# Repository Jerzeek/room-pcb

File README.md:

# Room Sensor

An open-source, mains-powered room sensor PCB based on the ESP32-C6. Measures CO2, temperature, humidity, illuminance, and presence, with a WS2812B LED status indicator. Supports both **ESPHome** (Wi-Fi / Home Assistant) and **Zigbee** firmware out of the box.

---

> **WARNING — MAINS AC VOLTAGE**
>
> This board connects directly to mains AC (100–240 V). Incorrect wiring or handling can cause **electric shock, fire, or death**. This project is intended for **experienced makers** who are comfortable working with mains-voltage electronics. Always work with the power disconnected. Comply with all local electrical codes. The authors accept no liability for any damage or injury.

---

## Features

- Direct mains AC input via onboard HLK-5M05 AC-DC converter (no external power brick needed)
- CO2, temperature, and humidity via CozIR sensor (NDIR CO2, UART)
- Ambient light via BH1750 (I2C, lux)
- Secondary temperature + humidity via AHT20 (I2C)
- Presence/occupancy detection via LD2410 mmWave radar (UART)
- Visual CO2 status indicator: 2× WS2812B addressable LEDs
- Polyfuse (F1) overcurrent protection
- Reset/factory-reset button (BOOT pin)
- ESP32-C6 SuperMini module — supports both Wi-Fi 6 and native Zigbee
- Two equal-priority firmware options: ESPHome and Zigbee (Arduino)

## Sensors

| Sensor | Part | Interface | Measures |
|---|---|---|---|
| CO2 (NDIR) | CozIR | UART (9600 baud) | CO2 (ppm), temperature, humidity |
| Ambient light | BH1750FVI-TR | I2C (0x23) | Illuminance (lux) |
| Temperature + humidity | AHT20 | I2C | Temperature (°C), humidity (%RH) |
| Presence / occupancy | LD2410 | UART (256000 baud) | Presence, moving/stationary targets |
| Status LEDs | WS2812B-2020 × 2 | GPIO (RMT) | CO2 level indicator |

## Hardware

### Main components

| Ref | Part | Description |
|---|---|---|
| U5 | ESP32-C6 SuperMini | Main MCU — Wi-Fi 6 + Zigbee |
| PS1 | HLK-5M05 | AC-DC converter, 100–240 V AC → 5 V DC |
| U1 | CozIR | NDIR CO2 / temp / humidity sensor |
| U2 | BH1750FVI-TR | Ambient light sensor |
| U3 | AHT20 | Temperature + humidity sensor |
| J4 | 5-pin header (1.27 mm) | LD2410 radar connection |
| D1, D2 | WS2812B-2020 | Addressable RGB LEDs |
| F1 | Polyfuse | Overcurrent protection |

### Versions

| Version | Notes |
|---|---|
| v4.1 | Current release — improved silkscreen |
| v4 | Production-ready layout |
| v3.1 | Earlier revision (3D model reference) |
| v3 | Initial working prototype |

## Building / Ordering

All files needed to order and assemble the PCB are in `pcb/production/`:

| File | Purpose |
|---|---|
| `room-pcb.zip` | Gerber + drill files — upload directly to your PCB fab (JLCPCB, PCBWay, etc.) |
| `bom.csv` | Bill of materials for component sourcing |
| `positions.csv` | Pick-and-place / component placement file |
| `designators.csv` | Designator reference |
| `netlist.ipc` | IPC-D-356 netlist for electrical testing |

KiCad source files are in `pcb/`.

## Firmware

### ESPHome (Wi-Fi / Home Assistant)

Configuration is in `code/esphome/room_sensor.yaml`. A custom ESPHome component for the CozIR sensor is included under `code/esphome/components/cozir/`.

1. Copy `room_sensor.yaml` and the `components/` directory to your ESPHome config folder.
2. Create a `secrets.yaml` with your `wifi_ssid` and `wifi_password`.
3. Flash via `esphome run room_sensor.yaml`.

The LED indicates CO2 level:

| Color | CO2 |
|---|---|
| Green | < 800 ppm (good) |
| Yellow | 800–1200 ppm (moderate) |
| Red | > 1200 ppm (poor) |

Calibration buttons are exposed to Home Assistant:
- **Calibrate Fresh Air (400 ppm)** — use outdoors in clean air
- **Calibrate Nitrogen (0 ppm)** — use with pure N2

### Zigbee (Arduino / esp32-arduino)

Sketch is in `code/combined_working_zigbee/combined_working_zigbee.ino`. Requires the Arduino ESP32 core (≥ 3.x) with Zigbee support.

**Before flashing:**
- In Arduino IDE → Tools → Zigbee Mode → select **Zigbee ED (End Device)**
- Select a partition scheme that includes Zigbee (e.g., *Zigbee 4MB with spiffs*)

The sketch exposes four Zigbee endpoints:

| Endpoint | Cluster | Data |
|---|---|---|
| 10 | CO2 (CarbonDioxide) | CO2 ppm |
| 11 | Temp + Humidity | Temperature °C, humidity %RH |
| 13 | Illuminance | Lux |
| 14 | Occupancy | Presence (boolean) |

Hold the BOOT button for 3 seconds to perform a Zigbee factory reset.

## Repository layout

```
room-pcb/
├── pcb/                  KiCad project files
│   └── production/       Gerbers, BOM, placement — ready to order
├── code/
│   ├── esphome/          ESPHome YAML + custom CozIR component
│   └── combined_working_zigbee/  Arduino Zigbee sketch
├── 3Dmodels/             STEP model of the enclosure / board
├── CHANGELOG.md
├── CONTRIBUTING.md
└── LICENSE
```

## License

Hardware (PCB and schematics) is licensed under the **CERN Open Hardware Licence Version 2 — Strongly Reciprocal (CERN OHL-S v2)**. See [LICENSE](LICENSE) for the full text.

Firmware is licensed under the same CERN OHL-S v2 unless a file header states otherwise.

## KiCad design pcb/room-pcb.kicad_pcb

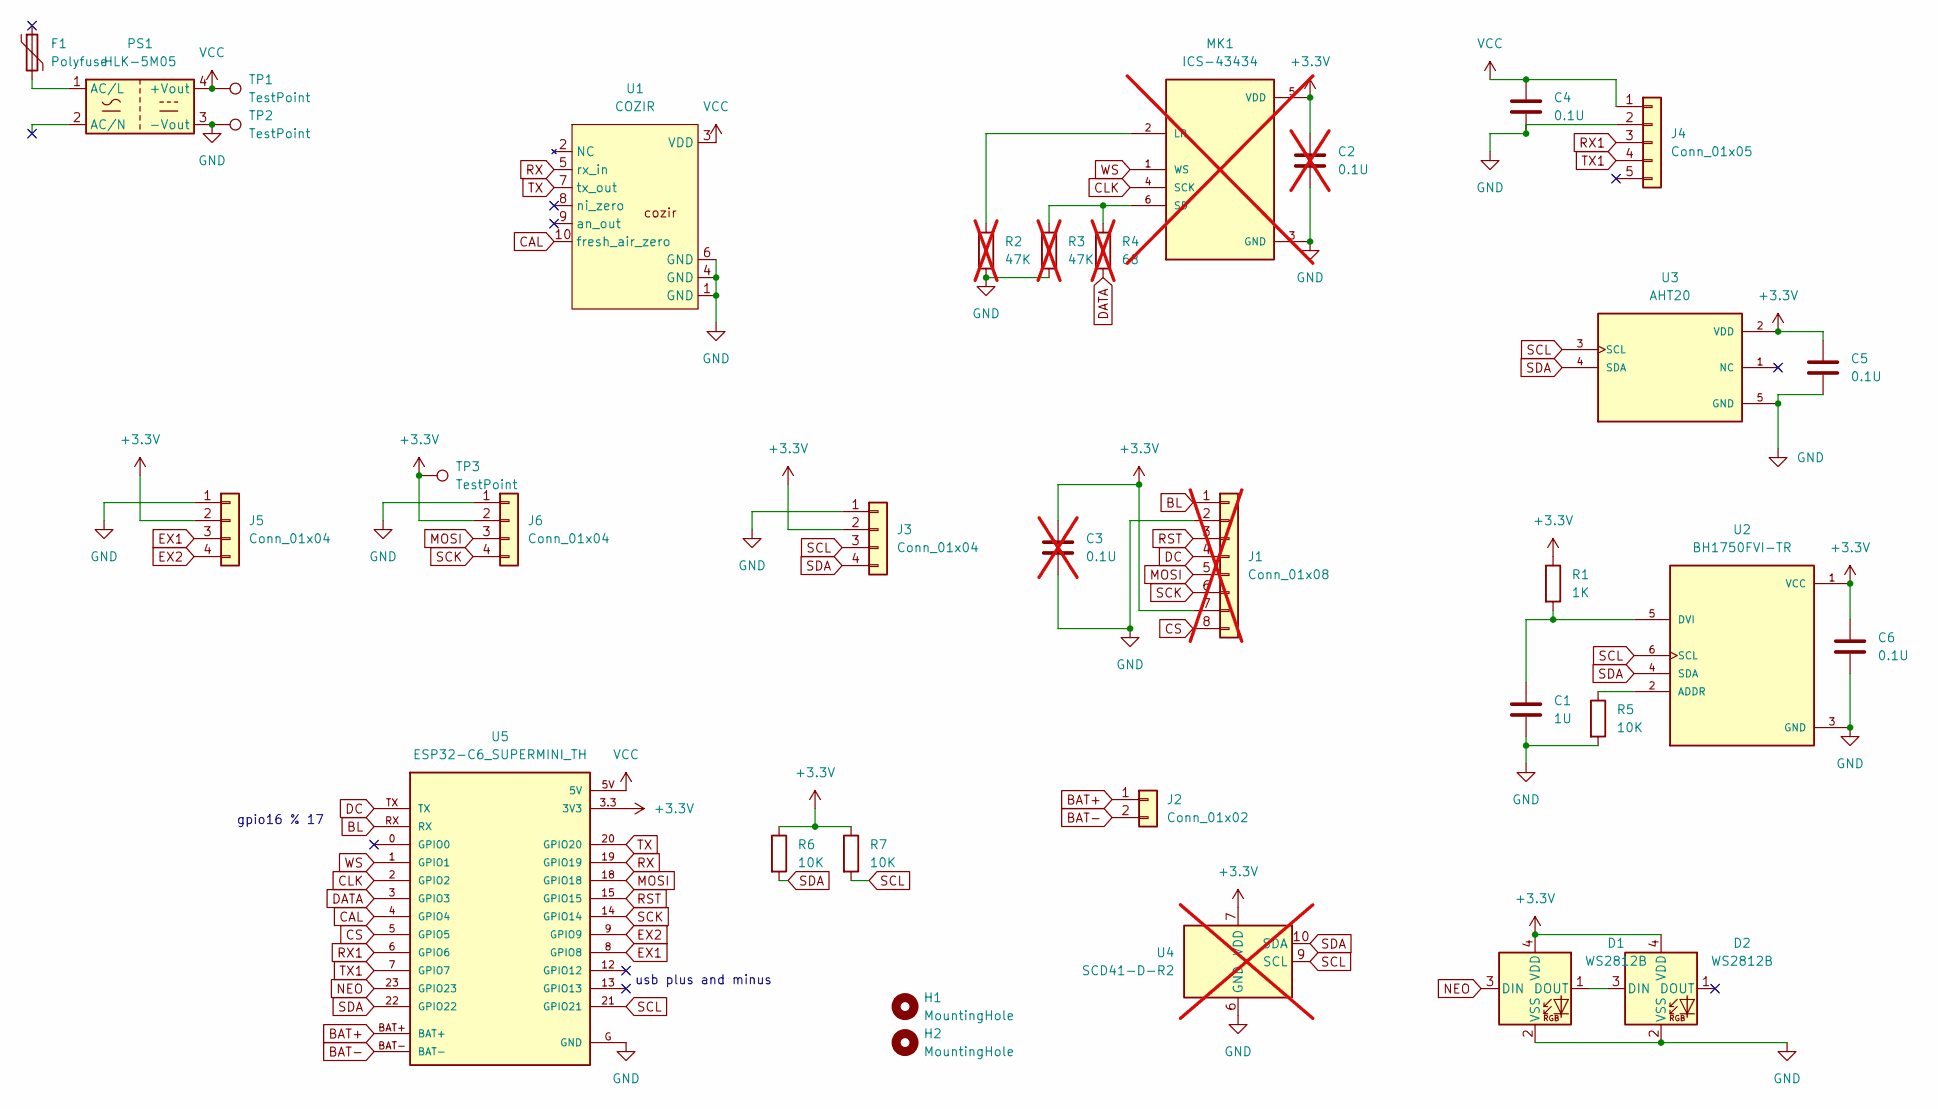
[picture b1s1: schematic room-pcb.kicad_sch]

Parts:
C1: 1U; C_0805_2012Metric
C2, C3: 0.1U; C_0805_2012Metric; not fitted
C4, C5, C6: 0.1U; C_0805_2012Metric
D1, D2: WS2812B; LED_WS2812B-2020_PLCC4_2.0x2.0mm
F1: Polyfuse; Fuse_Bourns_MF-RG300
H1, H2: MountingHole; MountingHole_3.2mm_M3
J1: Conn_01x08; Hirose_FH12-8S-0.5SH_1x08-1MP_P0.50mm_Horizontal; not fitted
J2: Conn_01x02; JST_PH_S2B-PH-SM4-TB_1x02-1MP_P2.00mm_Horizontal
J3: Conn_01x04; JST_SH_SM04B-SRSS-TB_1x04-1MP_P1.00mm_Horizontal
J4: Conn_01x05; PinHeader_1x05_P1.27mm_Vertical
J5, J6: Conn_01x04; PinHeader_1x04_P2.54mm_Vertical
MK1: ICS-43434; MIC_ICS-43434; not fitted
PS1: HLK-5M05; Converter_ACDC_Hi-Link_HLK-5Mxx
R1: 1K; R_0805_2012Metric
R2, R3: 47K; R_0805_2012Metric; not fitted
R4: 68; R_0805_2012Metric; not fitted
R5, R6, R7: 10K; R_0805_2012Metric
TP1, TP2, TP3: TestPoint; TestPoint_THTPad_D1.5mm_Drill0.7mm
U1: COZIR; cozir
U2: BH1750FVI-TR; XDCR_BH1750FVI-TR; PARTREV D
U3: AHT20; PSON100P300X300X110-6N; PARTREV V1.0
U4: SCD41-D-R2; Sensirion_SCD4x-1EP_10.1x10.1mm_P1.25mm_EP4.8x4.8mm; not fitted
U5: ESP32-C6_SUPERMINI_TH; MODULE_ESP32-C6_SUPERMINI_TH

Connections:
+3.3V: C2.1, C3.1, C5.1, C6.1, D1.4 (VDD), D2.4 (VDD), J1.7, J3.2, J5.2, J6.2, MK1.5 (VDD), R1.1, R6.1, R7.1, TP3.1, U2.1 (VCC), U3.2 (VDD), U4.7 (VDD), U4.19 (VDD), U5.3.3 (3V3)
BAT+: J2.1, U5.BAT+
BAT-: J2.2, U5.BAT-
BL: J1.1, U5.RX
CAL: U1.10 (fresh_air_zero), U5.4 (GPIO4)
CLK: MK1.4 (SCK), U5.2 (GPIO2)
CS: J1.8, U5.5 (GPIO5)
DATA: R4.2, U5.3 (GPIO3)
DC: J1.4, U5.TX
EX1: J5.3, U5.8 (GPIO8)
EX2: J5.4, U5.9 (GPIO9)
GND: C1.2, C2.2, C3.2, C4.2, C5.2, C6.2, D1.2 (VSS), D2.2 (VSS), J1.2, J3.1, J4.2, J5.1, J6.1, MK1.3 (GND), PS1.3 (-Vout), R2.2, R3.2, R5.2, TP2.1, U1.1 (GND), U1.4 (GND), U1.6 (GND), U2.3 (GND), U3.5 (GND), U4.6 (GND), U4.20 (GND), U4.21 (GND), U5.G (GND)
MOSI: J1.5, J6.3, U5.18 (GPIO18)
NEO: D1.3 (DIN), U5.23 (GPIO23)
unnamed: D1.1 (DOUT), D2.3 (DIN)
unnamed: MK1.2 (LR), R2.1
unnamed: MK1.6 (SD), R3.1, R4.1
unnamed: F1.2, PS1.1 (AC/L)
unnamed: R5.1, U2.2 (ADDR)
unnamed: C1.1, R1.2, U2.5 (DVI)
RST: J1.3, U5.15 (GPIO15)
RX: U1.5 (rx_in), U5.19 (GPIO19)
RX1: J4.3, U5.6 (GPIO6)
SCK: J1.6, J6.4, U5.14 (GPIO14)
SCL: J3.3, R7.2, U2.6 (SCL), U3.3 (SCL), U4.9 (SCL), U5.21 (GPIO21)
SDA: J3.4, R6.2, U2.4 (SDA), U3.4 (SDA), U4.10 (SDA), U5.22 (GPIO22)
TX: U1.7 (tx_out), U5.20 (GPIO20)
TX1: J4.4, U5.7 (GPIO7)
VCC: C4.1, J4.1, PS1.4 (+Vout), TP1.1, U1.3 (VDD), U5.5V
WS: MK1.1 (WS), U5.1 (GPIO1)

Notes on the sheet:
gpio16 % 17
usb plus and minus

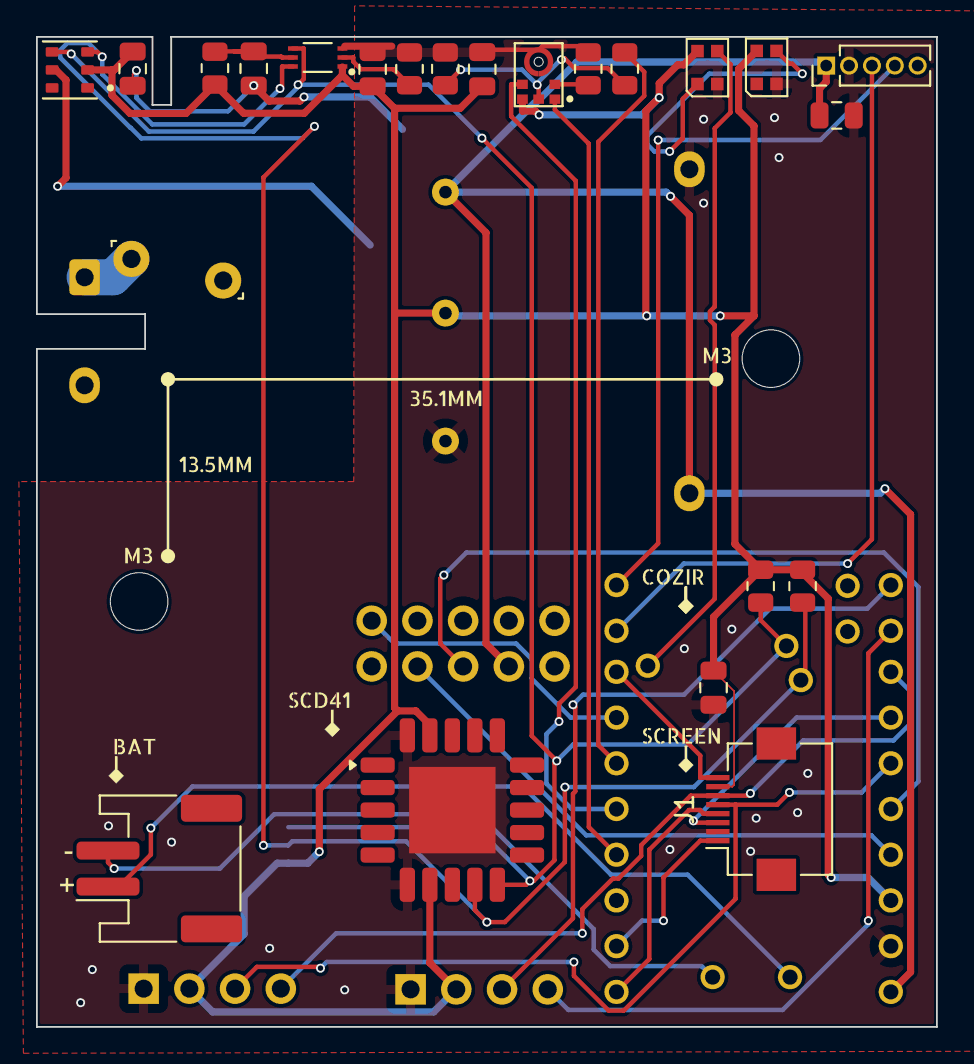
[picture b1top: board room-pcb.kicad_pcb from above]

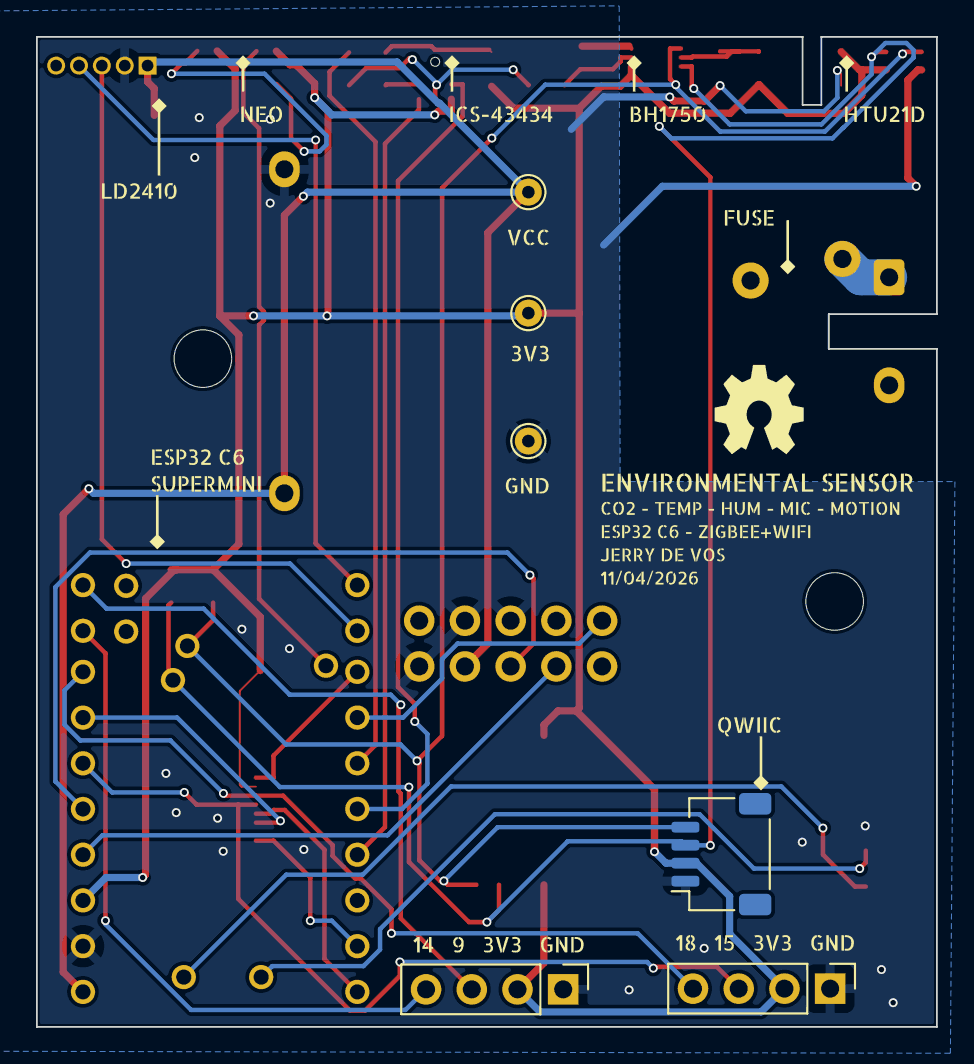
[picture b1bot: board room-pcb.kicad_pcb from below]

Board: 2 copper layers, 50.0 x 55.0 mm, 34 parts (7 on the bottom side), 30 nets.

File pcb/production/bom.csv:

Designator,Footprint,Quantity,Value,LCSC Part #
C1,0805,1,1U,
"C4, C5, C6",0805,3,0.1U,
"D1, D2",LED_WS2812B-2020_PLCC4_2.0x2.0mm,2,WS2812B,
F1,Fuse_Bourns_MF-RG300,1,Polyfuse,
J2,JST_PH_S2B-PH-SM4-TB_1x02-1MP_P2.00mm_Horizontal,1,Conn_01x02,
J3,JST_SH_SM04B-SRSS-TB_1x04-1MP_P1.00mm_Horizontal,1,Conn_01x04,
J4,PinHeader_1x05_P1.27mm_Vertical,1,Conn_01x05,
"J5, J6",PinHeader_1x04_P2.54mm_Vertical,2,Conn_01x04,
PS1,Converter_ACDC_Hi-Link_HLK-5Mxx,1,HLK-5M05,
R1,0805,1,1K,
"R5, R6, R7",0805,3,10K,
"TP1, TP2, TP3",TestPoint_THTPad_D1.5mm_Drill0.7mm,3,TestPoint,
U1,cozir,1,COZIR,
U2,XDCR_BH1750FVI-TR,1,BH1750FVI-TR,
U3,PSON100P300X300X110-6N,1,AHT20,
U5,MODULE_ESP32-C6_SUPERMINI_TH,1,ESP32-C6_SUPERMINI_TH,

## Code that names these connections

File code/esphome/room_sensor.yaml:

esphome:
  name: room-sensor3
  friendly_name: room_sensor3

esp32:
  board: esp32-c6-devkitc-1
  framework:
    type: esp-idf

# Enable logging
logger:

# Enable Home Assistant API
api:
  encryption:
    key: "x7dmEtUnraoTiORhJYHz7vtC5tRRsgen1eWqUg1EyWk="

ota:
  - platform: esphome
    password: "e07e7f460b2b8dd917edea576c4c2a43"

wifi:
  ssid: !secret wifi_ssid
  password: !secret wifi_password

  # Enable fallback hotspot (captive portal) in case wifi connection fails
  ap:
    ssid: "Room-Sensor Fallback Hotspot"
    password: "viXdy4Uy5Z67"

captive_portal:

external_components:
  - source:
      type: local
      path: components

uart:

  - id: uart_bus
    tx_pin: GPIO19
    rx_pin: GPIO20
    baud_rate: 9600

  - id: uart_bus_ld2410
    tx_pin: GPIO5
    rx_pin: GPIO7
    baud_rate: 256000 
    parity: NONE
    stop_bits: 1

i2c:
  sda: GPIO22
  scl: GPIO21

# Example configuration entry
ld2410:
  - uart_id: uart_bus_ld2410

light:
  - platform: esp32_rmt_led_strip
    rgb_order: GRB
    id: co2_led
    pin: GPIO23
    num_leds: 2
    chipset: ws2812
    name: "My Light"

binary_sensor:
  - platform: ld2410
    has_target:
      name: Presence
    # has_moving_target:
    #   name: Moving Target
    # has_still_target:
    #   name: Still Target
    # out_pin_presence_status:
    #   name: Out pin presence status

sensor:
  # - platform: ld2410
  #   light:
  #     name: Light
  #   moving_distance:
  #     name: Moving Distance
  #   still_distance:
  #     name: Still Distance
  #   moving_energy:
  #     name: Move Energy
  #   still_energy:
  #     name: Still Energy
  #   detection_distance:
  #     name: Detection Distance
  #   g0:
  #     move_energy:
  #       name: G0 move energy
  #     still_energy:
  #       name: G0 still energy
  #   g1:
  #     move_energy:
  #       name: G1 move energy
  #     still_energy:
  #       name: G1 still energy
  #   g2:
  #     move_energy:
  #       name: G2 move energy
  #     still_energy:
  #       name: G2 still energy
  #   g3:
  #     move_energy:
  #       name: G3 move energy
  #     still_energy:
  #       name: G3 still energy
  #   g4:
  #     move_energy:
  #       name: G4 move energy
  #     still_energy:
  #       name: G4 still energy
  #   g5:
  #     move_energy:
  #       name: G5 move energy
  #     still_energy:
  #       name: G5 still energy
  #   g6:
  #     move_energy:
  #       name: G6 move energy
  #     still_energy:
  #       name: G6 still energy
  #   g7:
  #     move_energy:
  #       name: G7 move energy
  #     still_energy:
  #       name: G7 still energy
  #   g8:
  #     move_energy:
  #       name: G8 move energy
  #     still_energy:
  #       name: G8 still energy
  - platform: cozir
    uart_id: uart_bus
    id: my_cozir  # Required for calibration actions
    co2:
      name: "Cozir CO2"
      filters:
      - exponential_moving_average:
          alpha: 0.1
          send_every: 2
          send_first_at: 1
      on_value_range:
          - below: 800.0
            then:
              - light.turn_on:
                  id: co2_led
                  brightness: 100%
                  red: 0.0
                  green: 0.7
                  blue: 0.0
          - above: 800.0
            below: 1200.0
            then:
              - light.turn_on:
                  id: co2_led
                  brightness: 100%
                  red: 0.8
                  green: 0.7
                  blue: 0.0
          - above: 1200.0
            then:
              - light.turn_on:
                  id: co2_led
                  brightness: 100%
                  red: 0.7
                  green: 0.0
                  blue: 0.0
    temperature:
      name: "Cozir Temperature"
      # Example configuration entry
      filters:
        - offset: -5.0
    humidity:
      name: "Cozir Humidity"
    update_interval: 30s
  - platform: bh1750
    name: "BH1750 Illuminance"
    address: 0x23
    update_interval: 60s
  - platform: aht10
    variant: AHT20
    temperature:
      name: "Room sensor Temperature"
      filters:
        - offset: -3.0
    humidity:
      name: "Room sensor Humidity"
    update_interval: 60s
button:
  - platform: template
    name: "Calibrate Fresh Air (400ppm)"
    on_press:
      - lambda: 'id(my_cozir)->calibrate_fresh_air();'
      
  - platform: template
    name: "Calibrate Nitrogen (0ppm)"
    on_press:
      - lambda: 'id(my_cozir)->calibrate_nitrogen();'

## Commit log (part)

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2026-01-22 new layout
2026-02-04 first order
2026-02-08 first order with cozir fix and i2c fix
2026-02-17 add quantile filter
2026-02-17 new layout order 2
2026-02-17 esphome code
2026-02-17 add pcb info
2026-02-17 added 3d model
2026-03-30 correct hole pcb
2026-04-10 v4.1
2026-04-10 with new gerbers
2026-04-11 nice silk now

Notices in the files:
README.md:
License: CERN OHL-S v2
